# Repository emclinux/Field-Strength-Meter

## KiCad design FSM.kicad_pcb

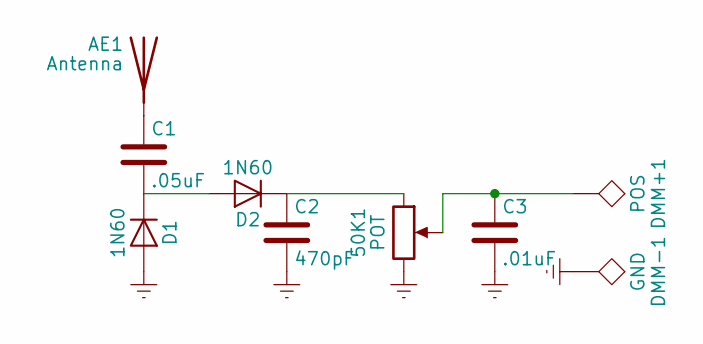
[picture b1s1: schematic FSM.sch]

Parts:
50K1: POT; Potentiometer_WirePads_largePads
AE1: Antenna; Banana_Jack_1Pin
C1: .05uF; C_Disc_D6.0mm_W2.5mm_P5.00mm
C2: 470pF; C_Disc_D6.0mm_W2.5mm_P5.00mm
C3: .01uF; C_Disc_D6.0mm_W2.5mm_P5.00mm
D1, D2: 1N60; D_DO-201AD_P5.08mm_Vertical_AnodeUp
DMM+1: POS; PINTST
DMM-1: GND; PINTST

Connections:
Earth: 50K1.3, C2.2, C3.2, D1.2 (A), DMM-1.1
unnamed: 50K1.1, C2.1, D2.1 (K)
unnamed: 50K1.2, C3.1, DMM+1.1
unnamed: AE1.1, C1.1
unnamed: C1.2, D1.1 (K), D2.2 (A)

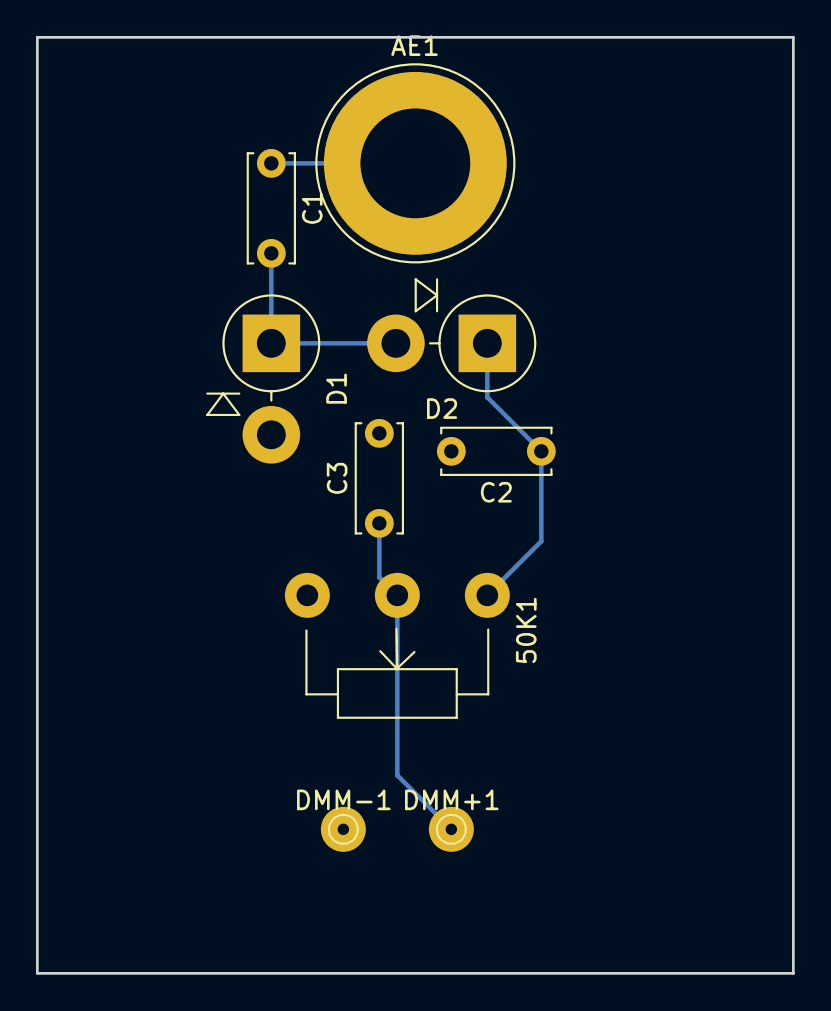
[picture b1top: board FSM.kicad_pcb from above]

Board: 2 copper layers, 42.0 x 52.0 mm, 9 parts (0 on the bottom side), 5 nets.
